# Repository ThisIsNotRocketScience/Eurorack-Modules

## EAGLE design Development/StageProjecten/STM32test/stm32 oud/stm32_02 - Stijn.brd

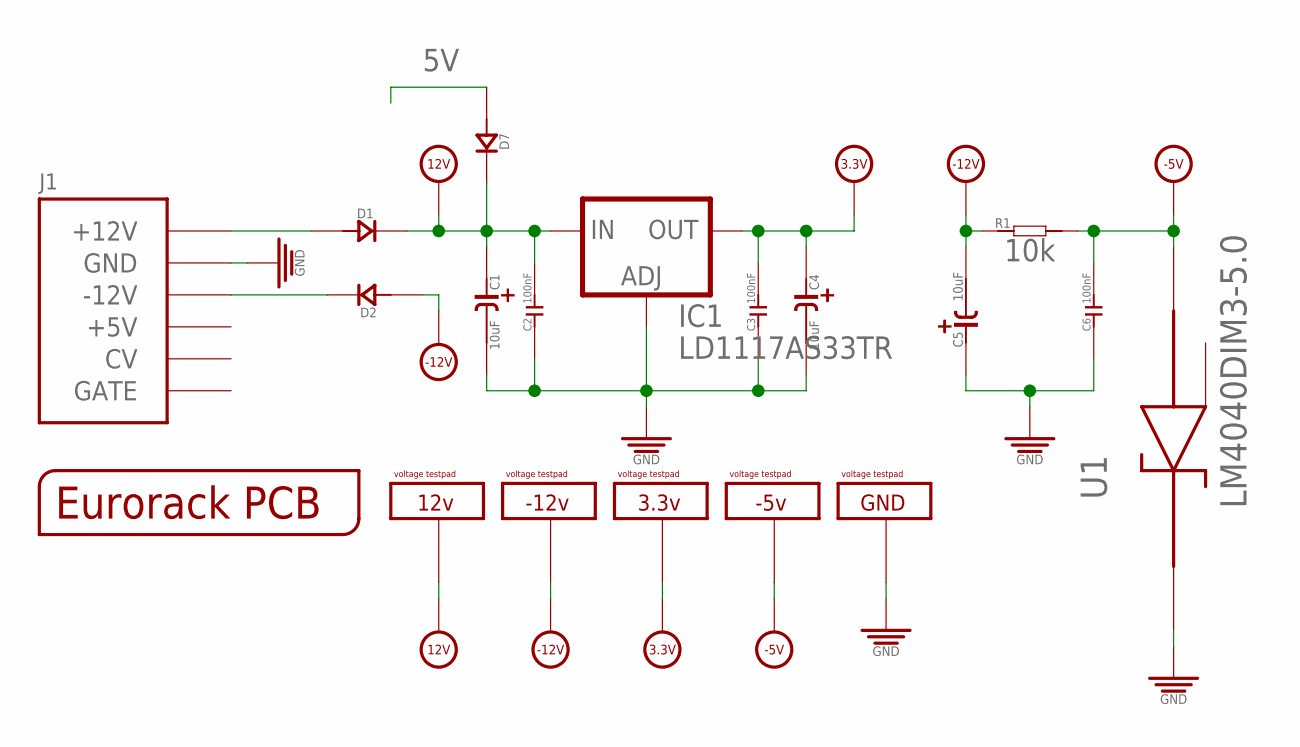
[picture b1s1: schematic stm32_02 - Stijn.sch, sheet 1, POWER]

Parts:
C1, C4, C5: 10uF; CASE-A_3216
C2, C3, C6: 100nF; C0603
D1, D2, D7: D-SMA; DO-214AC
IC1: LD1117AS33TR; SOT223
J1: POWERSHROUDED; POWER_16_SHROUDED
PCB1: EURORACK_PCB12HP; EURORACK12HPPCB
R1: 10k; R0603
U1: LM4040DIM3-5.0; SOT95P237X112-3N
U$7, U$8, U$37, U$38, U$43: VOLTAGETESTPAD; POWERTESTPAD

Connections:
3.3V: C3.2, C4.+ (1), IC1.2 (OUT), IC1.4 (OUT), U$37.P$1, U$37.P$2, U$37.P$3; also elsewhere on the board
5V: D7.1 (+); also elsewhere on the board
12V: C1.+ (1), C2.2, D1.2 (-), D7.2 (-), IC1.3 (IN), U$7.P$1, U$7.P$2, U$7.P$3; also elsewhere on the board
-5V: C6.2, R1.2, U1.2 (ANODE), U$38.P$1, U$38.P$2, U$38.P$3; also elsewhere on the board
-12V: C5.- (2), D2.1 (+), R1.1, U$8.P$1, U$8.P$2, U$8.P$3; also elsewhere on the board
GND: C1.- (2), C2.1, C3.1, C4.- (2), C5.+ (1), C6.1, IC1.1 (ADJ), J1.3 (GND), J1.4 (GND), J1.5 (GND), J1.6 (GND), J1.7 (GND), J1.8 (GND), U1.1 (CATHODE), U$43.P$1, U$43.P$2, U$43.P$3; also elsewhere on the board
unnamed: D2.2 (-), J1.1 (-12V), J1.2 (-12V)
unnamed: D1.1 (+), J1.9 (+12V), J1.10 (+12V)

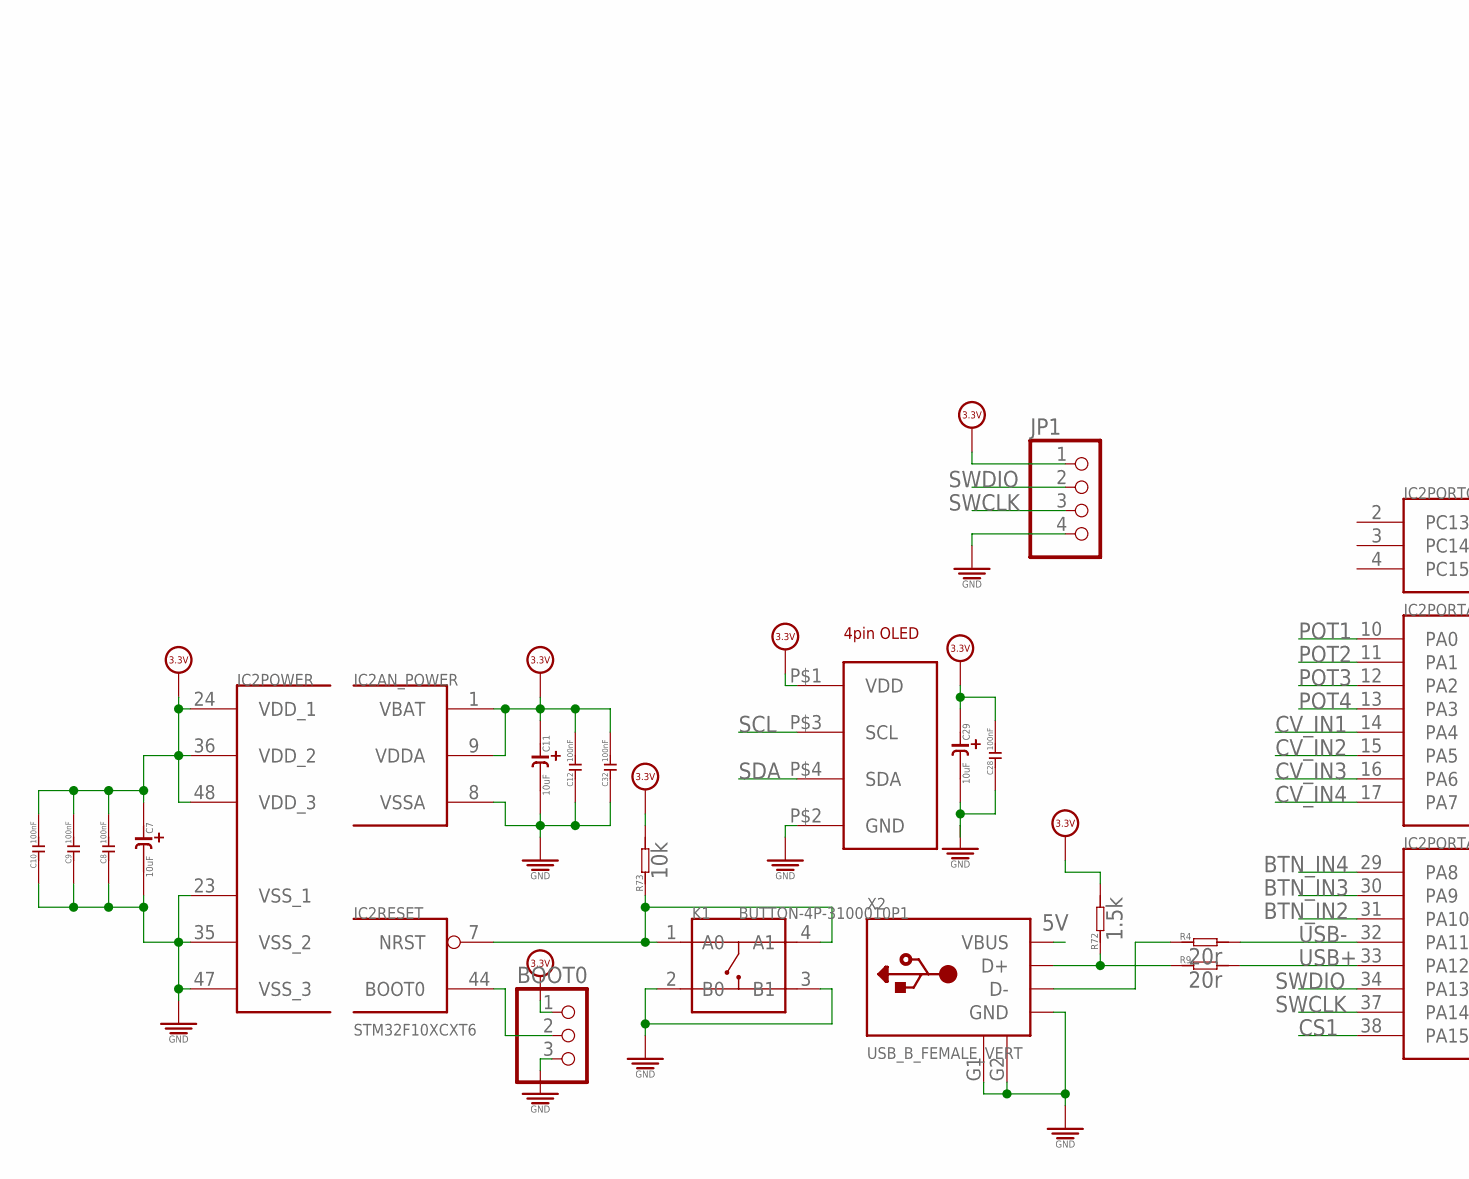
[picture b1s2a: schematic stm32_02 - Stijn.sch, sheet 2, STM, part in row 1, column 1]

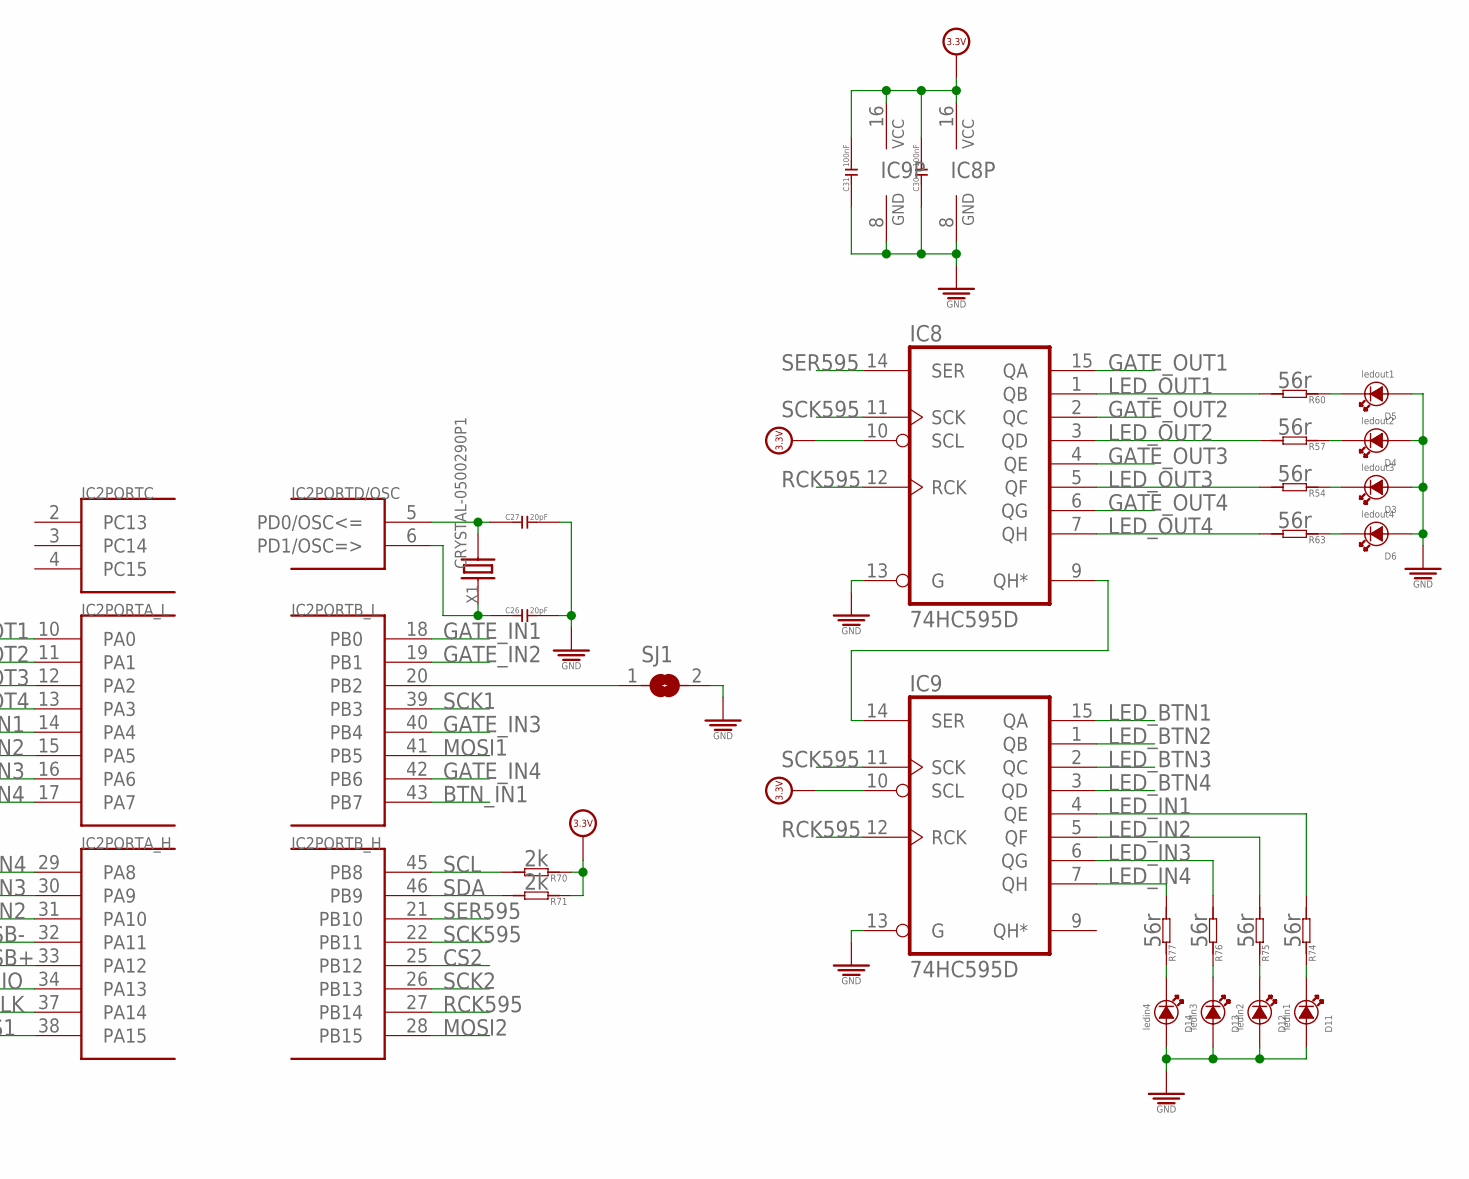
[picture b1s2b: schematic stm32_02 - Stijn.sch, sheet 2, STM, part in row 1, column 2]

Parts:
BOOT0: PINHD-1X3; 1X03
C7, C11, C29: 10uF; CASE-A_3216
C8, C9, C10, C12, C28, C30, C31, C32: 100nF; C0603
C26, C27: 20pF; C0603
D3, D4, D5, D6, D11, D12, D13, D14: LED3MM; 3MMLED
IC2: STM32F10XCXT6; TQFP48
IC8, IC9: 74HC595D; SO16
JP1: PINHD-1X4; 1X04
K1: BUTTON-4P-3100010P1; 4P-SMD-6.0X6.0X5.0H
R4, R9: 20r; R0603
R54, R57, R60, R63, R74, R75, R76, R77: 56r; R0603
R70, R71: 2k; R0603
R72: 1.5k; R0603
R73: 10k; R0603
SJ1: SJ
U$44: 4PIN_OLED; 1.3_4PIN_OLED
X1: CRYSTAL-0500290P1; 2P-SMD-5.0X3.2
X2: USB_B_FEMALE_VERT; USB_B_VERT

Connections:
3.3V: BOOT0.1, C7.+ (1), C8.2, C9.2, C10.2, C11.+ (1), C12.2, C28.2, C29.+ (1), C30.2, C31.2, C32.2, IC2.1 (VBAT), IC2.9 (VDDA), IC2.24 (VDD_1), IC2.36 (VDD_2), IC2.48 (VDD_3), IC8.10 (SCL), IC8.16 (VCC), IC9.10 (SCL), IC9.16 (VCC), JP1.1, R70.1, R71.1, R72.2, R73.2, U$44.P$1 (VDD); also elsewhere on the board
5V: X2.1 (VBUS); also elsewhere on the board
BTN_IN1: IC2.43 (PB7); also elsewhere on the board
BTN_IN2: IC2.31 (PA10); also elsewhere on the board
BTN_IN3: IC2.30 (PA9); also elsewhere on the board
BTN_IN4: IC2.29 (PA8); also elsewhere on the board
CS1: IC2.38 (PA15); also elsewhere on the board
CS2: IC2.25 (PB12); also elsewhere on the board
CV_IN1: IC2.14 (PA4); also elsewhere on the board
CV_IN2: IC2.15 (PA5); also elsewhere on the board
CV_IN3: IC2.16 (PA6); also elsewhere on the board
CV_IN4: IC2.17 (PA7); also elsewhere on the board
GATE_IN1: IC2.18 (PB0); also elsewhere on the board
GATE_IN2: IC2.19 (PB1); also elsewhere on the board
GATE_IN3: IC2.40 (PB4); also elsewhere on the board
GATE_IN4: IC2.42 (PB6); also elsewhere on the board
GATE_OUT1: IC8.15 (QA); also elsewhere on the board
GATE_OUT2: IC8.2 (QC); also elsewhere on the board
GATE_OUT3: IC8.4 (QE); also elsewhere on the board
GATE_OUT4: IC8.6 (QG); also elsewhere on the board
GND: BOOT0.3, C7.- (2), C8.1, C9.1, C10.1, C11.- (2), C12.1, C26.2, C27.2, C28.1, C29.- (2), C30.1, C31.1, C32.1, D3.+, D4.+, D5.+, D6.+, D11.+, D12.+, D13.+, D14.+, IC2.8 (VSSA), IC2.23 (VSS_1), IC2.35 (VSS_2), IC2.47 (VSS_3), IC8.8 (GND), IC8.13 (G), IC9.8 (GND), IC9.13 (G), JP1.4, K1.2 (B0), K1.3 (B1), SJ1.2, U$44.P$2 (GND), X2.4 (GND), X2.G1 (GND1), X2.G2 (GND2); also elsewhere on the board
LED_BTN1: IC9.15 (QA); also elsewhere on the board
LED_BTN2: IC9.1 (QB); also elsewhere on the board
LED_BTN3: IC9.2 (QC); also elsewhere on the board
LED_BTN4: IC9.3 (QD); also elsewhere on the board
LED_IN1: IC9.4 (QE), R74.2
LED_IN2: IC9.5 (QF), R75.2
LED_IN3: IC9.6 (QG), R76.2
LED_IN4: IC9.7 (QH), R77.2
LED_OUT1: IC8.1 (QB), R60.2
LED_OUT2: IC8.3 (QD), R57.2
LED_OUT3: IC8.5 (QF), R54.2
LED_OUT4: IC8.7 (QH), R63.2
MOSI1: IC2.41 (PB5); also elsewhere on the board
MOSI2: IC2.28 (PB15); also elsewhere on the board
unnamed: D3.-, R54.1
unnamed: IC2.32 (PA11), R4.2
unnamed: D6.-, R63.1
unnamed: IC2.33 (PA12), R9.2
unnamed: C27.1, IC2.5 (PD0/OSC<=), X1.2
unnamed: C26.1, IC2.6 (PD1/OSC=>), X1.1
unnamed: D4.-, R57.1
unnamed: D5.-, R60.1
unnamed: IC2.20 (PB2), SJ1.1
unnamed: BOOT0.2, IC2.44 (BOOT0)
unnamed: IC8.9 (QH*), IC9.14 (SER)
unnamed: D11.-, R74.1
unnamed: D12.-, R75.1
unnamed: D13.-, R76.1
unnamed: D14.-, R77.1
POT1: IC2.10 (PA0); also elsewhere on the board
POT2: IC2.11 (PA1); also elsewhere on the board
POT3: IC2.12 (PA2); also elsewhere on the board
POT4: IC2.13 (PA3); also elsewhere on the board
RCK595: IC2.27 (PB14), IC8.12 (RCK), IC9.12 (RCK)
RESET: IC2.7 (NRST), K1.1 (A0), K1.4 (A1), R73.1
SCK1: IC2.39 (PB3); also elsewhere on the board
SCK2: IC2.26 (PB13); also elsewhere on the board
SCK595: IC2.22 (PB11), IC8.11 (SCK), IC9.11 (SCK)
SCL: IC2.45 (PB8), R70.2, U$44.P$3 (SCL)
SDA: IC2.46 (PB9), R71.2, U$44.P$4 (SDA)
SER595: IC2.21 (PB10), IC8.14 (SER)
SWCLK: IC2.37 (PA14), JP1.3
SWDIO: IC2.34 (PA13), JP1.2
USB+: R9.1, R72.1, X2.3 (D+)
USB-: R4.1, X2.2 (D-)

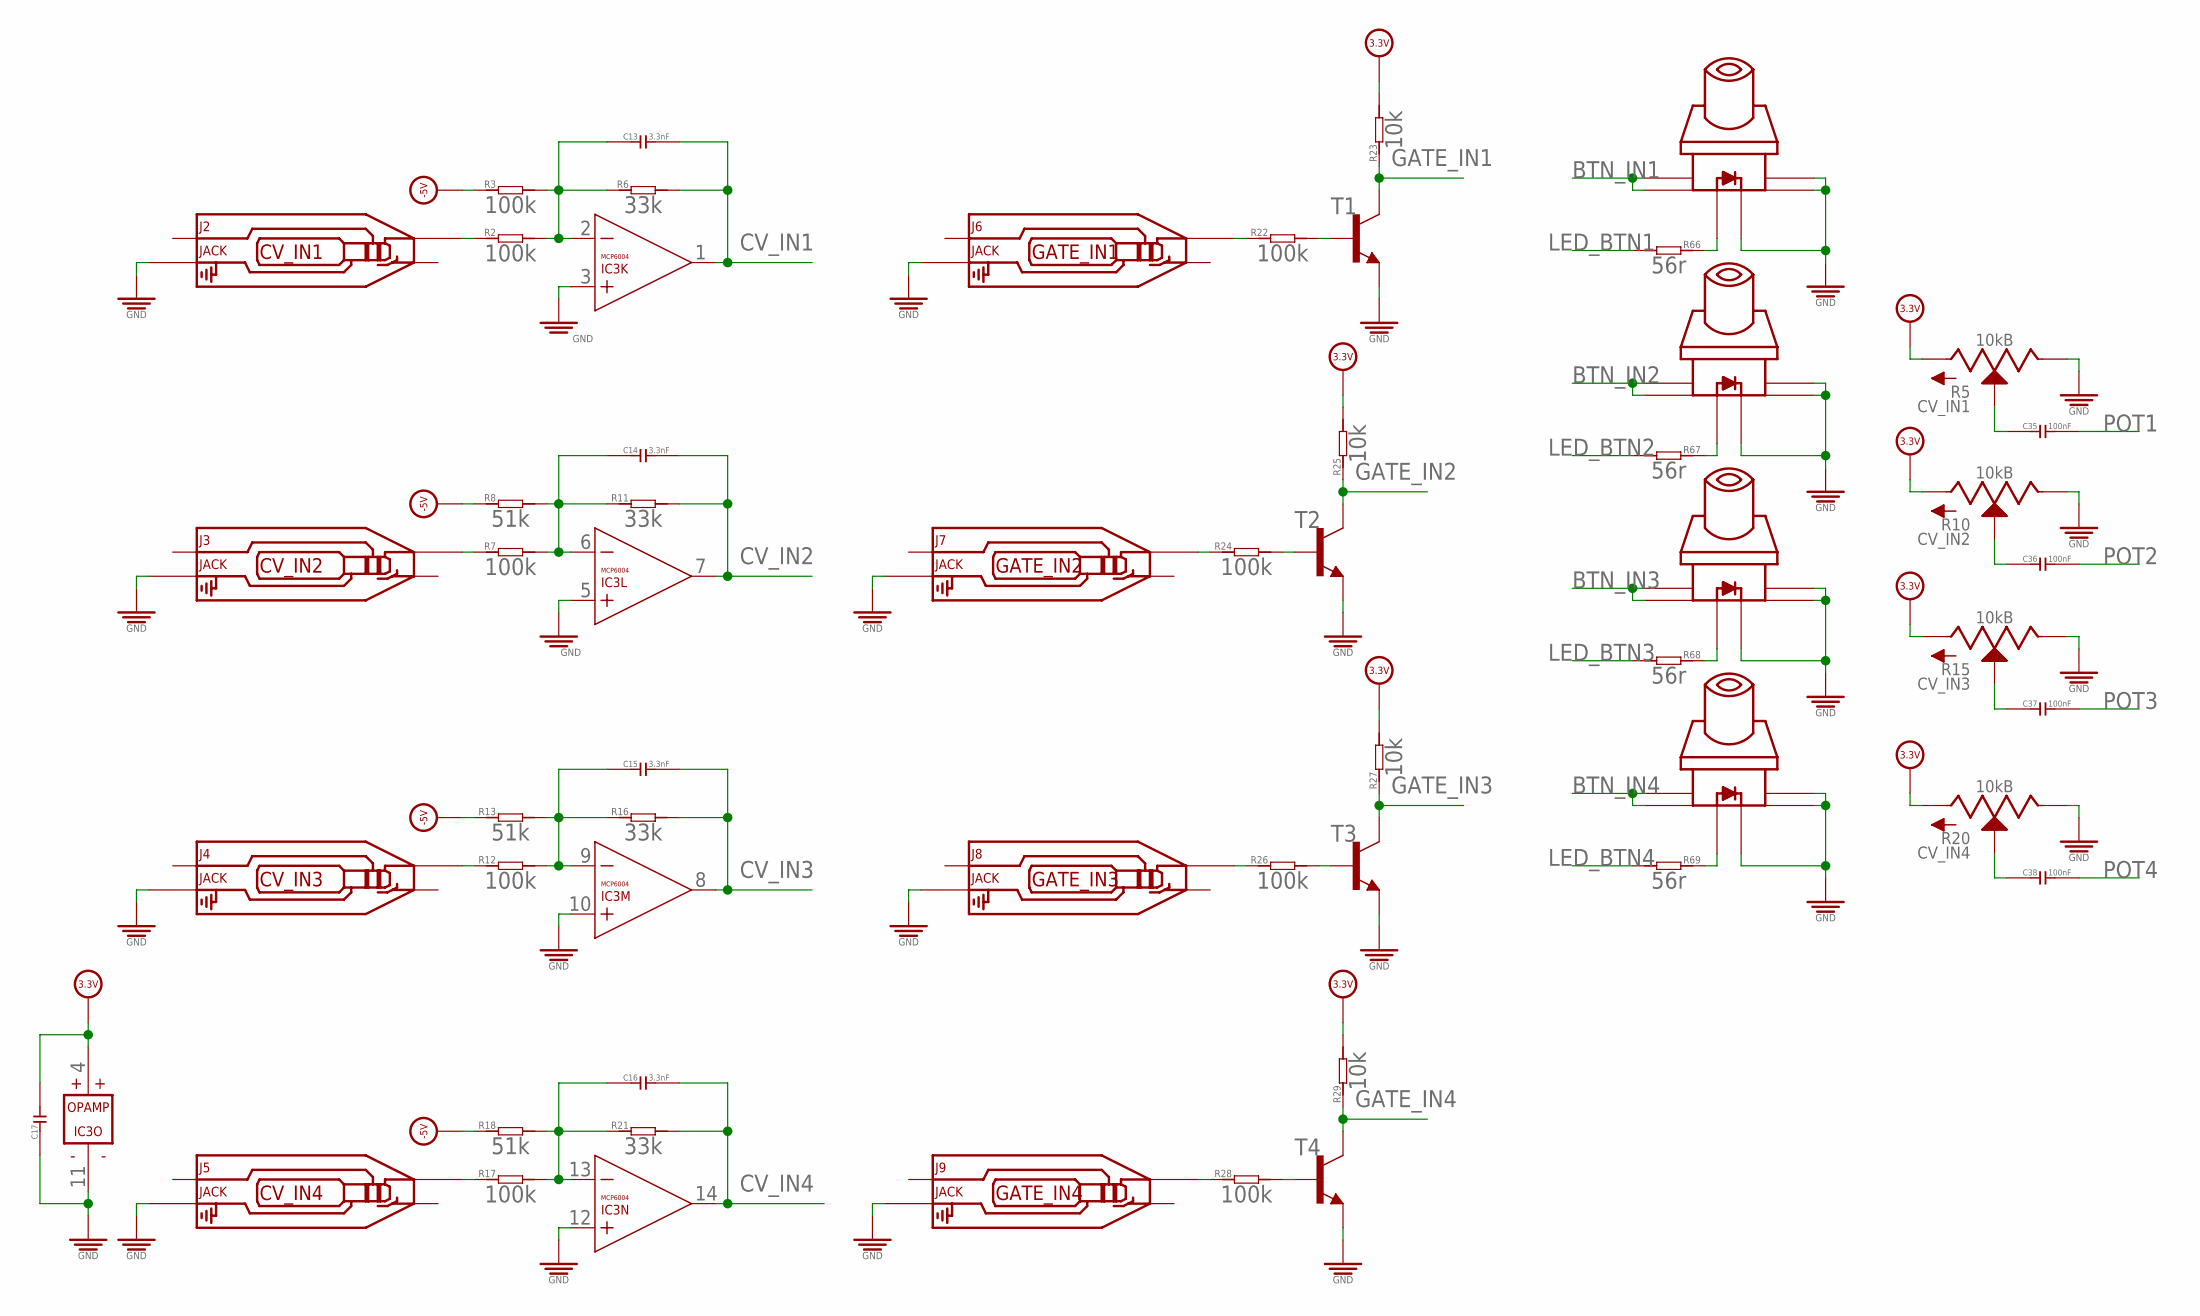
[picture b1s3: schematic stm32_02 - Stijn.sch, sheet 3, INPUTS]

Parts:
C13, C14, C15, C16: 3.3nF; C0603
C17: C-0603; C0603
C35, C36, C37, C38: 100nF; C0603
IC3: MCP6004; SO14
J2, J3, J4, J5, J6, J7, J8, J9: JACK; 3.5MM-JACK-SWITCH-13MM-NOHOLES
R2, R3, R7, R12, R17, R22, R24, R26, R28: 100k; R0603
R5, R10, R15, R20: 10kB; ALPS_POT_SQUAREHOLES
R6, R11, R16, R21: 33k; R0603
R8, R13, R18: 51k; R0603
R23, R25, R27, R29: 10k; R0603
R66, R67, R68, R69: 56r; R0603
S1, S2, S3, S4: SWITCH_W_LED_PB6149L-X-102BLUE; PB6149L
T1, T2, T3, T4: MMBT3904LT1-NPN-SOT23-BEC; SOT23-BEC

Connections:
3.3V: C17.2, IC3.4 (V+), R5.P$3 (A), R10.P$3 (A), R15.P$3 (A), R20.P$3 (A), R23.2, R25.2, R27.2, R29.2; also elsewhere on the board
-5V: R3.1, R8.1, R13.1, R18.1; also elsewhere on the board
BTN_IN1: S1.1, S1.2; also elsewhere on the board
BTN_IN2: S2.1, S2.2; also elsewhere on the board
BTN_IN3: S3.1, S3.2; also elsewhere on the board
BTN_IN4: S4.1, S4.2; also elsewhere on the board
CV_IN1: C13.2, IC3.1 (OUT), R6.2; also elsewhere on the board
CV_IN2: C14.2, IC3.7 (OUT), R11.2; also elsewhere on the board
CV_IN3: C15.2, IC3.8 (OUT), R16.2; also elsewhere on the board
CV_IN4: C16.2, IC3.14 (OUT), R21.2; also elsewhere on the board
GATE_IN1: R23.1, T1.C; also elsewhere on the board
GATE_IN2: R25.1, T2.C; also elsewhere on the board
GATE_IN3: R27.1, T3.C; also elsewhere on the board
GATE_IN4: R29.1, T4.C; also elsewhere on the board
GND: C17.1, IC3.3 (+IN), IC3.5 (+IN), IC3.10 (+IN), IC3.11 (V-), IC3.12 (+IN), J2.RING_B@1 (RING), J2.RING_T@3 (RING), J3.RING_B@1 (RING), J3.RING_T@3 (RING), J4.RING_B@1 (RING), J4.RING_T@3 (RING), J5.RING_B@1 (RING), J5.RING_T@3 (RING), J6.RING_B@1 (RING), J6.RING_T@3 (RING), J7.RING_B@1 (RING), J7.RING_T@3 (RING), J8.RING_B@1 (RING), J8.RING_T@3 (RING), J9.RING_B@1 (RING), J9.RING_T@3 (RING), R5.P$1 (E), R10.P$1 (E), R15.P$1 (E), R20.P$1 (E), S1.3, S1.4, S1.LEDNEG (NEG), S2.3, S2.4, S2.LEDNEG (NEG), S3.3, S3.4, S3.LEDNEG (NEG), S4.3, S4.4, S4.LEDNEG (NEG), T1.E, T2.E, T3.E, T4.E; also elsewhere on the board
LED_BTN1: R66.2; also elsewhere on the board
LED_BTN2: R67.2; also elsewhere on the board
LED_BTN3: R68.2; also elsewhere on the board
LED_BTN4: R69.2; also elsewhere on the board
unnamed: C35.1, R5.P$2 (S)
unnamed: J2.TIP_B@1 (TIP), J2.TIP_T@3 (TIP), R2.1
unnamed: C13.1, IC3.2 (-IN), R2.2, R3.2, R6.1
unnamed: J7.TIP_B@1 (TIP), J7.TIP_T@3 (TIP), R24.1
unnamed: C36.1, R10.P$2 (S)
unnamed: J3.TIP_B@1 (TIP), J3.TIP_T@3 (TIP), R7.1
unnamed: C14.1, IC3.6 (-IN), R7.2, R8.2, R11.1
unnamed: R24.2, T2.B
unnamed: C37.1, R15.P$2 (S)
unnamed: J4.TIP_B@1 (TIP), J4.TIP_T@3 (TIP), R12.1
unnamed: C15.1, IC3.9 (-IN), R12.2, R13.2, R16.1
unnamed: J8.TIP_B@1 (TIP), J8.TIP_T@3 (TIP), R26.1
unnamed: C38.1, R20.P$2 (S)
unnamed: J5.TIP_B@1 (TIP), J5.TIP_T@3 (TIP), R17.1
unnamed: C16.1, IC3.13 (-IN), R17.2, R18.2, R21.1
unnamed: R26.2, T3.B
unnamed: J6.TIP_B@1 (TIP), J6.TIP_T@3 (TIP), R22.1
unnamed: R22.2, T1.B
unnamed: J9.TIP_B@1 (TIP), J9.TIP_T@3 (TIP), R28.1
unnamed: R28.2, T4.B
unnamed: R69.1, S4.LEDPOS (POS)
unnamed: R68.1, S3.LEDPOS (POS)
unnamed: R67.1, S2.LEDPOS (POS)
unnamed: R66.1, S1.LEDPOS (POS)
POT1: C35.2; also elsewhere on the board
POT2: C36.2; also elsewhere on the board
POT3: C37.2; also elsewhere on the board
POT4: C38.2; also elsewhere on the board

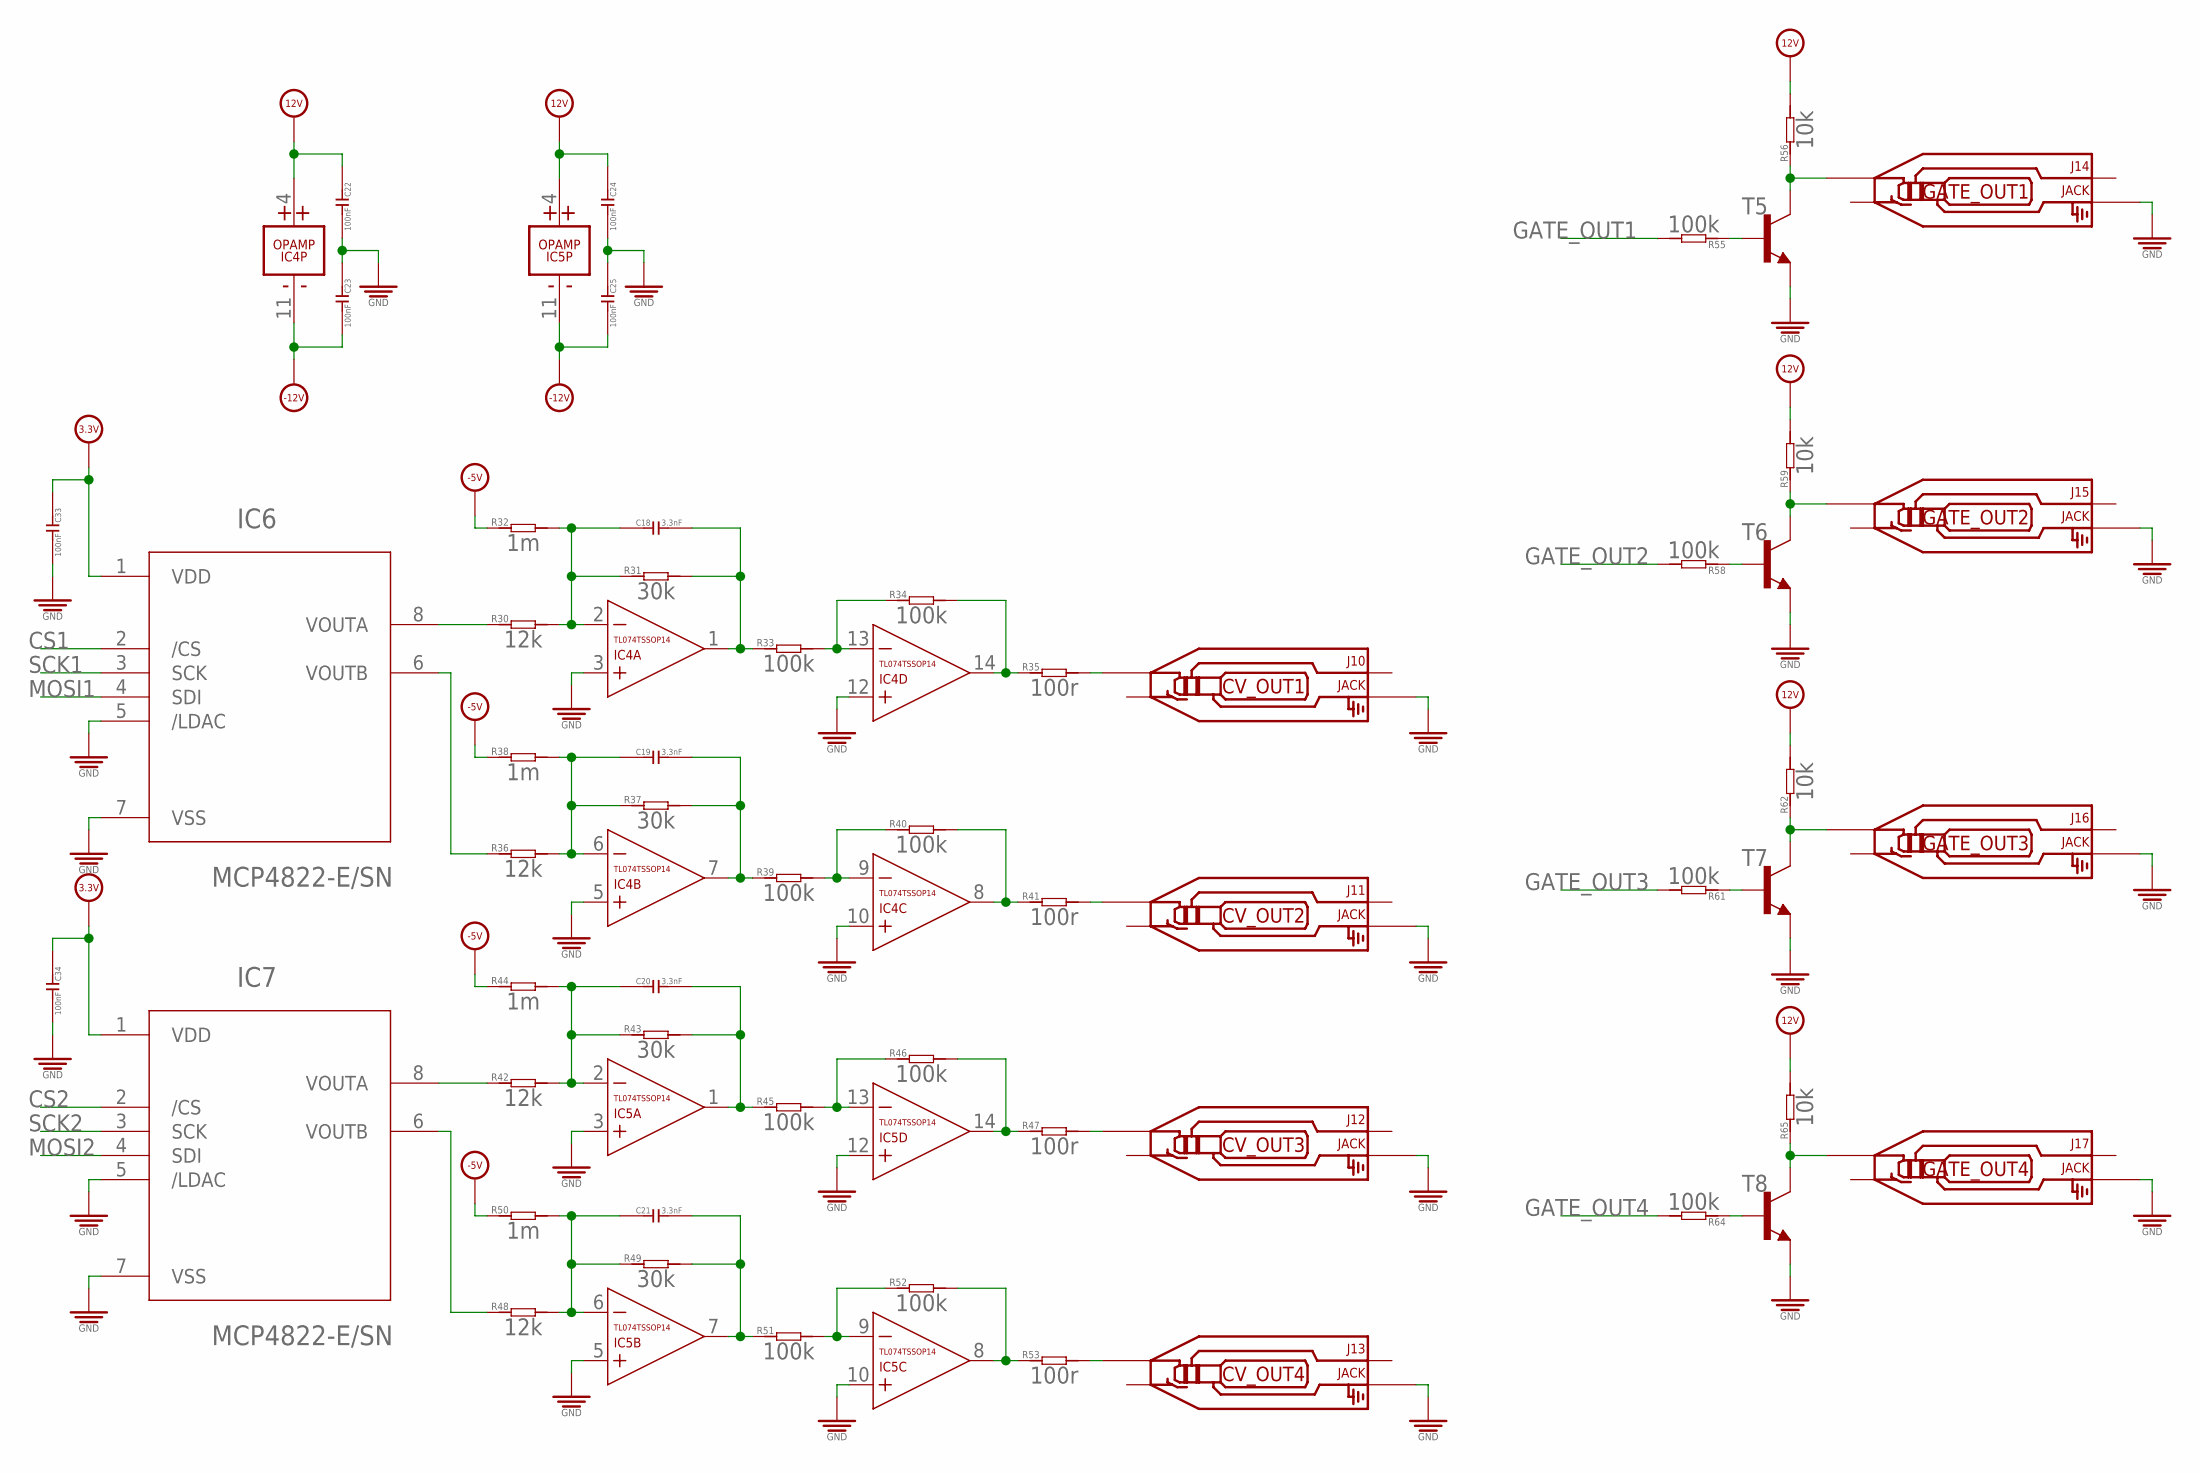
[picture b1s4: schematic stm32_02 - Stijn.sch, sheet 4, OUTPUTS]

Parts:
C18, C19, C20, C21: 3.3nF; C0603
C22, C23, C24, C25, C33, C34: 100nF; C0603
IC4, IC5: TL074TSSOP14; TSSOP14
IC6, IC7: MCP4822-E/SN; SOIC8-N_MC
J10, J11, J12, J13, J14, J15, J16, J17: JACK; 3.5MM-JACK-SWITCH-13MM-NOHOLES
R30, R36, R42, R48: 12k; R0603
R31, R37, R43, R49: 30k; R0603
R32, R38, R44, R50: 1m; R0603
R33, R34, R39, R40, R45, R46, R51, R52, R55, R58, R61, R64: 100k; R0603
R35, R41, R47, R53: 100r; R0603
R56, R59, R62, R65: 10k; R0603
T5, T6, T7, T8: MMBT3904LT1-NPN-SOT23-BEC; SOT23-BEC

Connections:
3.3V: C33.1, C34.1, IC6.1 (VDD), IC7.1 (VDD); also elsewhere on the board
12V: C22.1, C24.1, IC4.4 (V+), IC5.4 (V+), R56.2, R59.2, R62.2, R65.2; also elsewhere on the board
-5V: R32.1, R38.1, R44.1, R50.1; also elsewhere on the board
-12V: C23.2, C25.2, IC4.11 (V-), IC5.11 (V-); also elsewhere on the board
CS1: IC6.2 (/CS); also elsewhere on the board
CS2: IC7.2 (/CS); also elsewhere on the board
GATE_OUT1: R55.2; also elsewhere on the board
GATE_OUT2: R58.2; also elsewhere on the board
GATE_OUT3: R61.2; also elsewhere on the board
GATE_OUT4: R64.2; also elsewhere on the board
GND: C22.2, C23.1, C24.2, C25.1, C33.2, C34.2, IC4.3 (+IN), IC4.5 (+IN), IC4.10 (+IN), IC4.12 (+IN), IC5.3 (+IN), IC5.5 (+IN), IC5.10 (+IN), IC5.12 (+IN), IC6.5 (/LDAC), IC6.7 (VSS), IC7.5 (/LDAC), IC7.7 (VSS), J10.RING_B@1 (RING), J10.RING_T@3 (RING), J11.RING_B@1 (RING), J11.RING_T@3 (RING), J12.RING_B@1 (RING), J12.RING_T@3 (RING), J13.RING_B@1 (RING), J13.RING_T@3 (RING), J14.RING_B@1 (RING), J14.RING_T@3 (RING), J15.RING_B@1 (RING), J15.RING_T@3 (RING), J16.RING_B@1 (RING), J16.RING_T@3 (RING), J17.RING_B@1 (RING), J17.RING_T@3 (RING), T5.E, T6.E, T7.E, T8.E; also elsewhere on the board
MOSI1: IC6.4 (SDI); also elsewhere on the board
MOSI2: IC7.4 (SDI); also elsewhere on the board
unnamed: C18.1, IC4.2 (-IN), R30.2, R31.1, R32.2
unnamed: C18.2, IC4.1 (OUT), R31.2, R33.1
unnamed: J10.TIP_B@1 (TIP), J10.TIP_T@3 (TIP), R35.2
unnamed: IC4.13 (-IN), R33.2, R34.1
unnamed: IC4.14 (OUT), R34.2, R35.1
unnamed: IC6.8 (VOUTA), R30.1
unnamed: C19.1, IC4.6 (-IN), R36.2, R37.1, R38.2
unnamed: C19.2, IC4.7 (OUT), R37.2, R39.1
unnamed: IC4.9 (-IN), R39.2, R40.1
unnamed: IC4.8 (OUT), R40.2, R41.1
unnamed: IC6.6 (VOUTB), R36.1
unnamed: J11.TIP_B@1 (TIP), J11.TIP_T@3 (TIP), R41.2
unnamed: C20.1, IC5.2 (-IN), R42.2, R43.1, R44.2
unnamed: C20.2, IC5.1 (OUT), R43.2, R45.1
unnamed: IC5.13 (-IN), R45.2, R46.1
unnamed: IC5.14 (OUT), R46.2, R47.1
unnamed: IC7.8 (VOUTA), R42.1
unnamed: J12.TIP_B@1 (TIP), J12.TIP_T@3 (TIP), R47.2
unnamed: C21.1, IC5.6 (-IN), R48.2, R49.1, R50.2
unnamed: C21.2, IC5.7 (OUT), R49.2, R51.1
unnamed: IC5.9 (-IN), R51.2, R52.1
unnamed: IC5.8 (OUT), R52.2, R53.1
unnamed: IC7.6 (VOUTB), R48.1
unnamed: J13.TIP_B@1 (TIP), J13.TIP_T@3 (TIP), R53.2
unnamed: R55.1, T5.B
unnamed: J14.TIP_B@1 (TIP), J14.TIP_T@3 (TIP), R56.1, T5.C
unnamed: R58.1, T6.B
unnamed: J15.TIP_B@1 (TIP), J15.TIP_T@3 (TIP), R59.1, T6.C
unnamed: R61.1, T7.B
unnamed: J16.TIP_B@1 (TIP), J16.TIP_T@3 (TIP), R62.1, T7.C
unnamed: R64.1, T8.B
unnamed: J17.TIP_B@1 (TIP), J17.TIP_T@3 (TIP), R65.1, T8.C
SCK1: IC6.3 (SCK); also elsewhere on the board
SCK2: IC7.3 (SCK); also elsewhere on the board

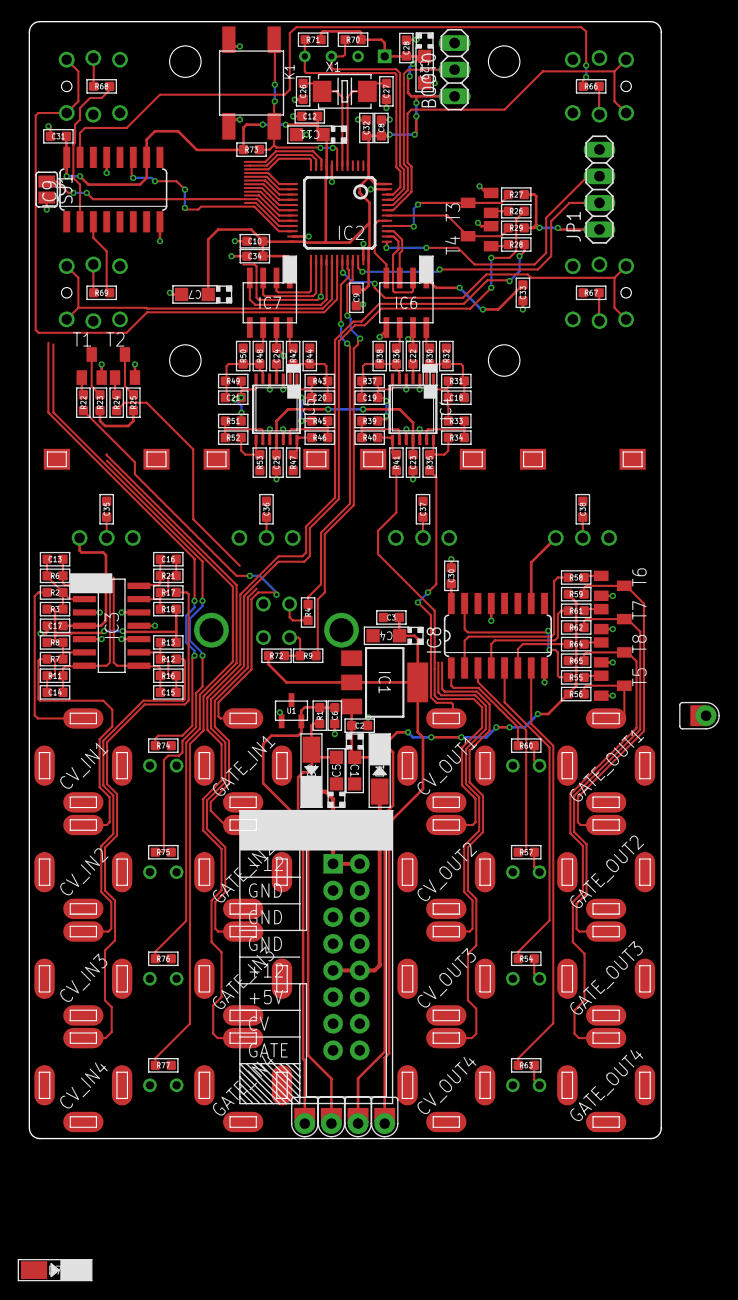
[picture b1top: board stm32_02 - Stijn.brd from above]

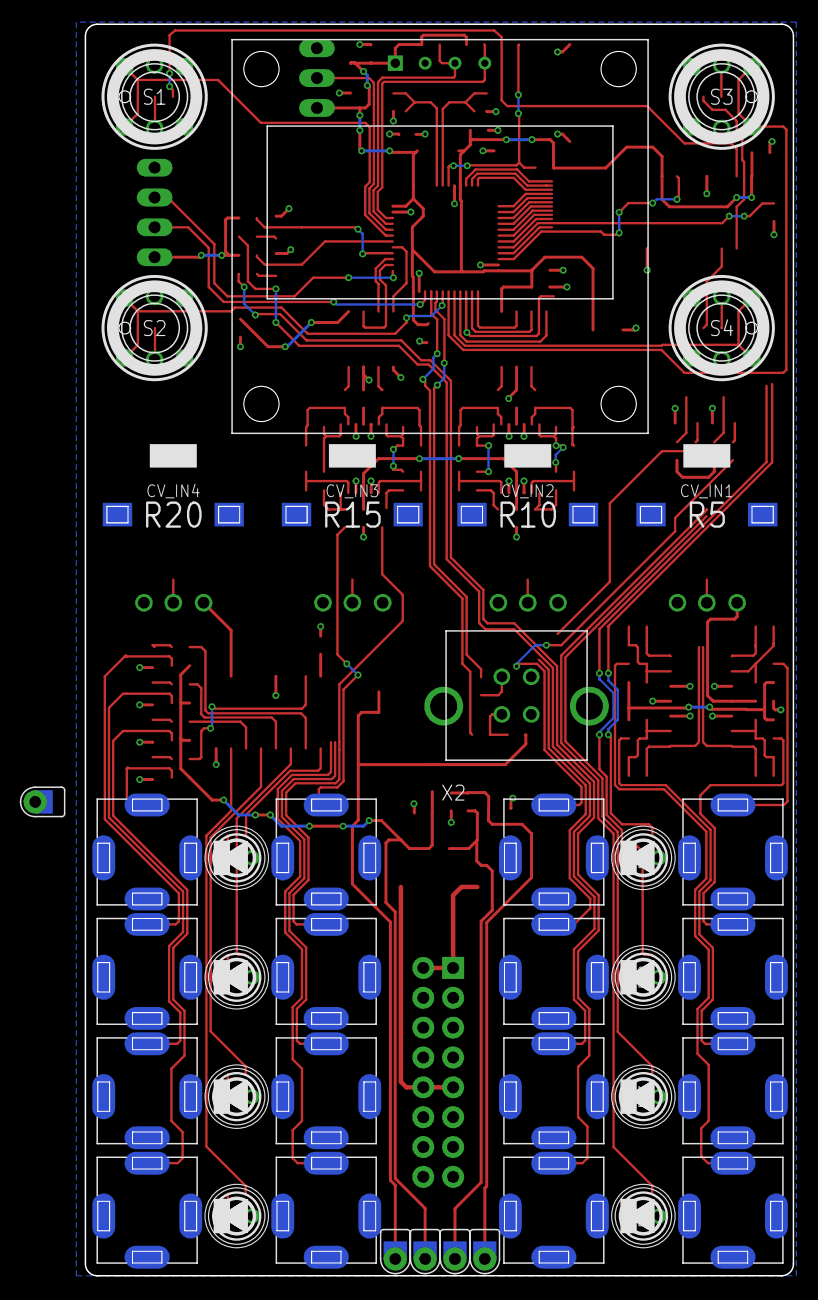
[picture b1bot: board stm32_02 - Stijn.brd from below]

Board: 2 copper layers, 60.2 x 106.5 mm, 176 parts (34 on the bottom side), 127 nets.

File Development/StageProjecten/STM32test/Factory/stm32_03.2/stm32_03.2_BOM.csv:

Comment,Designator,Footprint,LCSC Part #
10uF,"C1, C11, C4, C5, C7, C29",CASE-A_3216,
100nF,"C10, C12, C2, C22, C23, C24, C25, C3, C6, C8, C9, C28, C30, C31, C32, C33, C34, C35, C36, C37, C38, C39",C0603,
3.3nF,"C13, C14, C15, C16, C18, C19, C20, C21",C0603,
,"C17",C0603,
20pF,"C26, C27",C0603,
,"D1, D2, D7",DO-214AC,
LD1117AS33TR,"IC1",SOT223,
STM32F10XCXT6,"IC2",TQFP48,
MCP6004,"IC3",SO14,
TL074TSSOP14,"IC4, IC5",TSSOP14,
MCP4822-E/SN,"IC6, IC7",SOIC8-N_MC,
POWERSHROUDED,"J1",POWER_16_SHROUDED,
JACK,"J10, J11, J12, J13, J14, J15, J16, J17, J2, J3, J4, J5, J6, J7, J8, J9",3.5MM-JACK-SWITCH-13MM-NOHOLES,
10k,"R1, R23, R25, R27, R29, R56, R59, R62, R65, R73",R0603,
33k,"R11, R16, R21, R6",R0603,
100k,"R12, R17, R2, R22, R24, R26, R28, R3, R33, R34, R39, R40, R45, R46, R51, R52, R55, R58, R61, R64, R7",R0603,
51k,"R13, R18, R8",R0603,
12k,"R30, R36, R42, R48",R0603,
30k,"R31, R37, R43, R49",R0603,
1m,"R32, R38, R44, R50",R0603,
100r,"R35, R41, R47, R53",R0603,
2k,"R70, R71",R0603,
1.5k,"R72",R0603,
56r,"R63, R54, R57, R60, R74, R75, R76, R77, R66, R67, R68, R69",R0603,
20r,"R4, R9",R0603,
560r,"R14, R19",R0603,
10kB,"R10, R15, R20, R5",ALPS_POT_SQUAREHOLES,
,"T1, T2, T3, T4, T5, T6, T7, T8",SOT23-BEC,
LM4040DIM3-5.0,"U1",SOT95P237X112-3N,
EURORACK_PCB12HP,"PCB1",EURORACK12HPPCB,
VOLTAGETESTPAD,"U$7, U$8, U$37, U$38",POWERTESTPAD,
4PIN_OLED,"U$44",1.3_4PIN_OLED,
SWITCH_W_LED_PB6149L-X-102BLUE,"S1, S2, S3, S4",PB6149L,
CRYSTAL-0500290P1,"X1",2P-SMD-5.0X3.2,
USB_B_FEMALE_VERT,"X2",USB_B_VERT,
,"SJ1",SJ,
,"BOOT0",1X03,
BUTTON-4P-3100010P1,"K1",4P-SMD-6.0X6.0X5.0H,
74HC595D,"IC8, IC9",SO16,
,"D6, D3, D4, D5, D11, D12, D13, D14",3MMLED,
,"JP1",1X04,
RED,"D8, D9",LED0603,
GNDLOOP,"U$59",GROUNDLOOP,

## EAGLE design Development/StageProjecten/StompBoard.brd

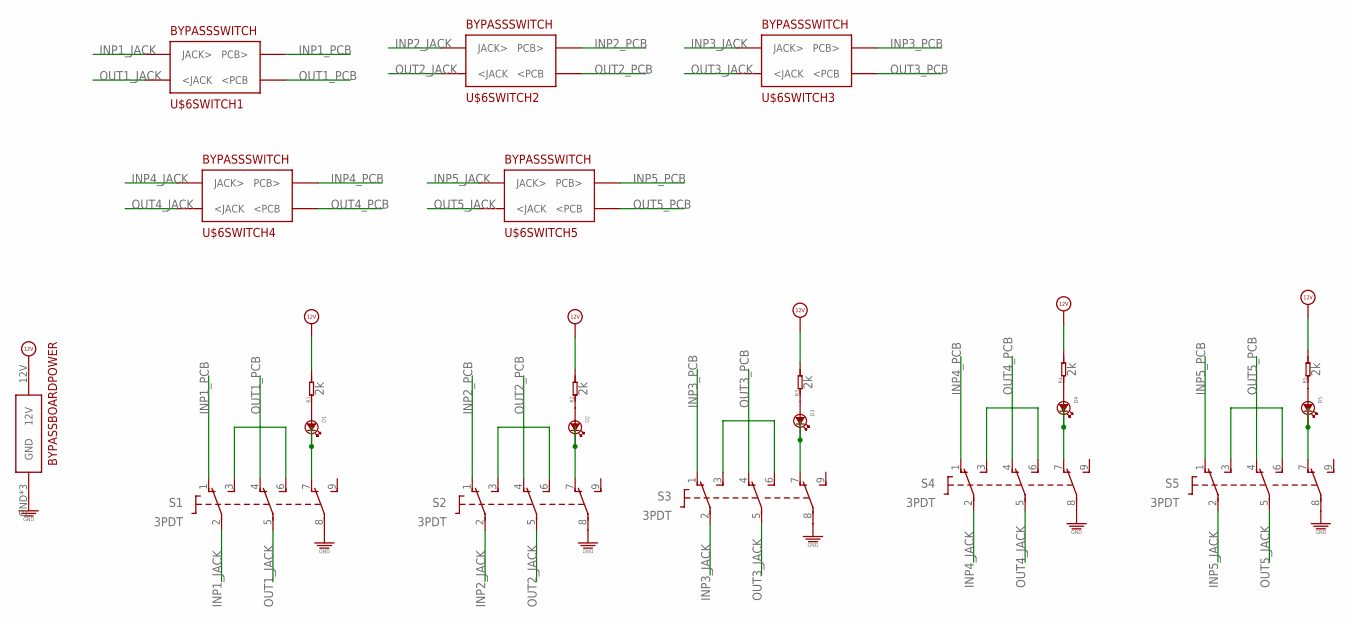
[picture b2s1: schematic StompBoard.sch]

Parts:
D1, D2, D3, D4, D5: LED3MM; 3MMLED
R1, R2, R3, R4, R5: 2k; R0603
S1, S2, S3, S4, S5: 3PDT
U$6: 5STOMPBOARD; BYPASSBOARD

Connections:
12V: R1.2, R2.2, R3.2, R4.2, R5.2, U$6.12V
GND: S1.8 (P3), S2.8 (P3), S3.8 (P3), S4.8 (P3), S5.8 (P3), U$6.GND, U$6.GND2 (GND), U$6.GND3 (GND)
INP1_JACK: S1.2 (P1), U$6.P$3 (JACK>)
INP1_PCB: S1.1 (O1), U$6.P$4 (PCB>)
INP2_JACK: S2.2 (P1), U$6.P$7 (JACK>)
INP2_PCB: S2.1 (O1), U$6.P$8 (PCB>)
INP3_JACK: S3.2 (P1), U$6.P$11 (JACK>)
INP3_PCB: S3.1 (O1), U$6.P$12 (PCB>)
INP4_JACK: S4.2 (P1), U$6.P$15 (JACK>)
INP4_PCB: S4.1 (O1), U$6.P$16 (PCB>)
INP5_JACK: S5.2 (P1), U$6.P$19 (JACK>)
INP5_PCB: S5.1 (O1), U$6.P$20 (PCB>)
unnamed: S1.3 (S1), S1.6 (S2)
unnamed: S2.3 (S1), S2.6 (S2)
unnamed: D1.-, S1.7 (O3)
unnamed: D1.+, R1.1
unnamed: D2.-, S2.7 (O3)
unnamed: D2.+, R2.1
unnamed: S3.3 (S1), S3.6 (S2)
unnamed: D3.-, S3.7 (O3)
unnamed: D3.+, R3.1
unnamed: S4.3 (S1), S4.6 (S2)
unnamed: D4.-, S4.7 (O3)
unnamed: D4.+, R4.1
unnamed: S5.3 (S1), S5.6 (S2)
unnamed: D5.-, S5.7 (O3)
unnamed: D5.+, R5.1
OUT1_JACK: S1.5 (P2), U$6.P$1 (<JACK)
OUT1_PCB: S1.4 (O2), U$6.P$2 (<PCB)
OUT2_JACK: S2.5 (P2), U$6.P$5 (<JACK)
OUT2_PCB: S2.4 (O2), U$6.P$6 (<PCB)
OUT3_JACK: S3.5 (P2), U$6.P$9 (<JACK)
OUT3_PCB: S3.4 (O2), U$6.P$10 (<PCB)
OUT4_JACK: S4.5 (P2), U$6.P$13 (<JACK)
OUT4_PCB: S4.4 (O2), U$6.P$14 (<PCB)
OUT5_JACK: S5.5 (P2), U$6.P$17 (<JACK)
OUT5_PCB: S5.4 (O2), U$6.P$18 (<PCB)

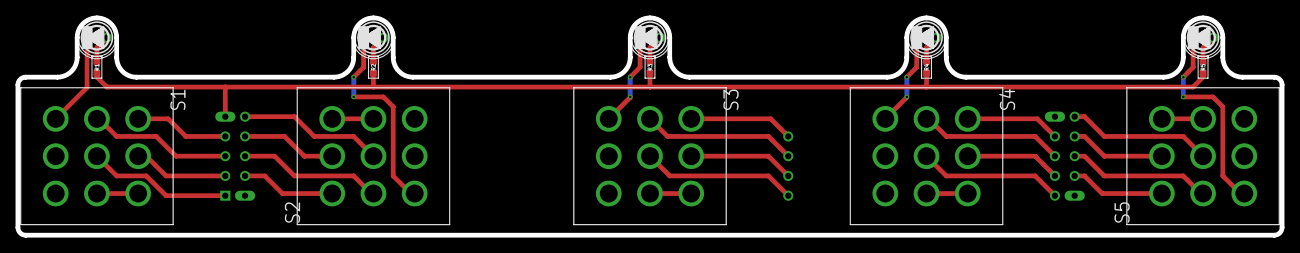
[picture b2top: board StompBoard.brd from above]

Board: 2 copper layers, 162.6 x 27.9 mm, 16 parts (0 on the bottom side), 37 nets.
